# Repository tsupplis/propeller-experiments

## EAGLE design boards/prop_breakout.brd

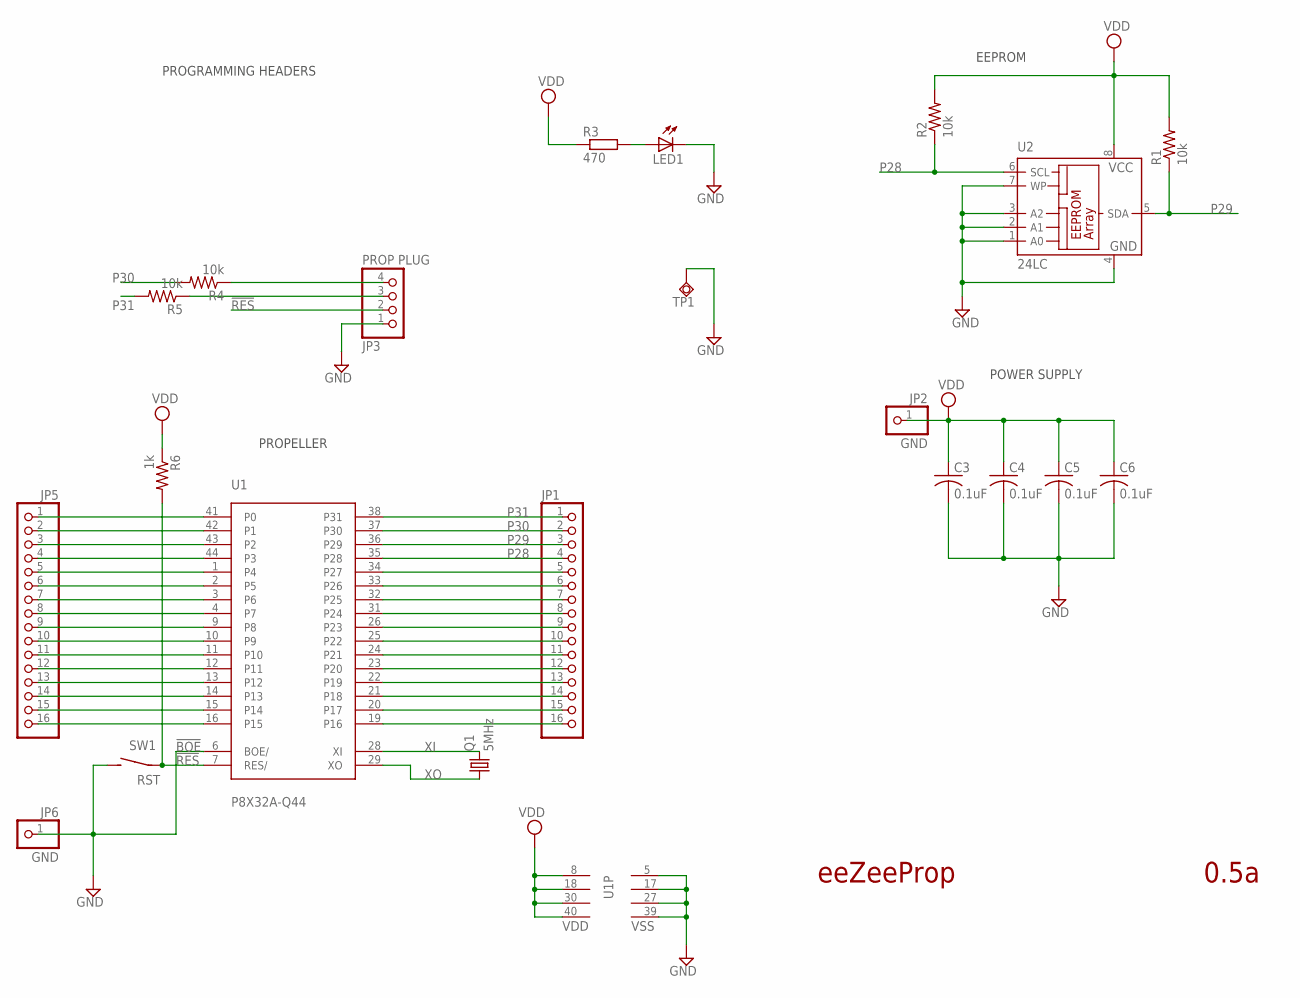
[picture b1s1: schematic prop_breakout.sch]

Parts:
C3, C4, C5, C6: 0.1uF; C0805; PARTNO 0603YC104KAT2A
JP1, JP5: PINHD-1X16_2.54-S; 1X16-S
JP2, JP6: GND; 1X01
JP3: PROP PLUG; 1X04-S
LED1: 0; CHIPLED_1206
Q1: 5MHz; HC49U-V; PARTNO HC49US-5.000MABJ-UB
R1, R2: 10k; R0805; PARTNO ERJ-3GEYJ103V
R3: 470; R0805
R4, R5: 10k; R0805; PARTNO RC0603JR-071KL
R6: 1k; R0805; PARTNO RC0603JR-071KL
SW1: RST; 6MMTACTILE_RECT; PARTNO MJTP1243
TP1: TPSQTP20R; TP20R
U1: P8X32A-Q44; PARTNO P8X32A-Q44
U2: 24LC; SO-08; MPN CAT24C256WI-GT3

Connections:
!RES: JP3.2, R6.2, SW1.P$1, U1.7 (RES/)
GND: C3.2, C4.2, C5.2, C6.2, JP3.1, JP6.1, LED1.C, SW1.P$2 (S), TP1.TP, U1.5 (VSS), U1.6 (BOE/), U1.17 (VSS), U1.27 (VSS), U1.39 (VSS), U2.1 (A0), U2.2 (A1), U2.3 (A2), U2.4 (GND), U2.7 (WP)
unnamed: JP5.1, U1.41 (P0)
unnamed: JP5.2, U1.42 (P1)
unnamed: JP5.3, U1.43 (P2)
unnamed: JP5.4, U1.44 (P3)
unnamed: LED1.A, R3.2
unnamed: JP5.5, U1.1 (P4)
unnamed: JP5.6, U1.2 (P5)
unnamed: JP5.7, U1.3 (P6)
unnamed: JP5.8, U1.4 (P7)
unnamed: JP5.9, U1.9 (P8)
unnamed: JP5.10, U1.10 (P9)
unnamed: JP5.11, U1.11 (P10)
unnamed: JP5.12, U1.12 (P11)
unnamed: JP5.13, U1.13 (P12)
unnamed: JP5.14, U1.14 (P13)
unnamed: JP5.15, U1.15 (P14)
unnamed: JP5.16, U1.16 (P15)
unnamed: JP1.5, U1.34 (P27)
unnamed: JP1.6, U1.33 (P26)
unnamed: JP1.7, U1.32 (P25)
unnamed: JP1.8, U1.31 (P24)
unnamed: JP1.9, U1.26 (P23)
unnamed: JP1.10, U1.25 (P22)
unnamed: JP1.11, U1.24 (P21)
unnamed: JP1.12, U1.23 (P20)
unnamed: JP1.13, U1.22 (P19)
unnamed: JP1.14, U1.21 (P18)
unnamed: JP1.15, U1.20 (P17)
unnamed: JP1.16, U1.19 (P16)
P28: JP1.4, R2.1, U1.35 (P28), U2.6 (SCL)
P29: JP1.3, R1.1, U1.36 (P29), U2.5 (SDA)
P30: JP1.2, R4.2, U1.37 (P30)
P31: JP1.1, R5.2, U1.38 (P31)
RXI: JP3.4, R4.1
TXO: JP3.3, R5.1
VDD: C3.1, C4.1, C5.1, C6.1, JP2.1, R1.2, R2.2, R3.1, R6.1, U1.8 (VDD), U1.18 (VDD), U1.30 (VDD), U1.40 (VDD), U2.8 (VCC)
XI: Q1.2, U1.28 (XI)
XO: Q1.1, U1.29 (XO)

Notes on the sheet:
!BOE
eeZeeProp
0.5a
POWER SUPPLY
PROGRAMMING HEADERS
EEPROM
PROPELLER

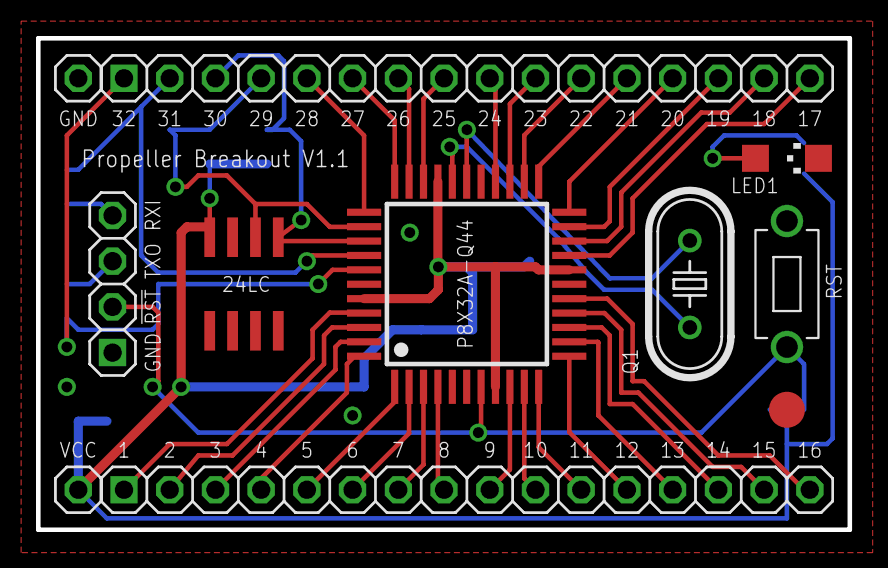
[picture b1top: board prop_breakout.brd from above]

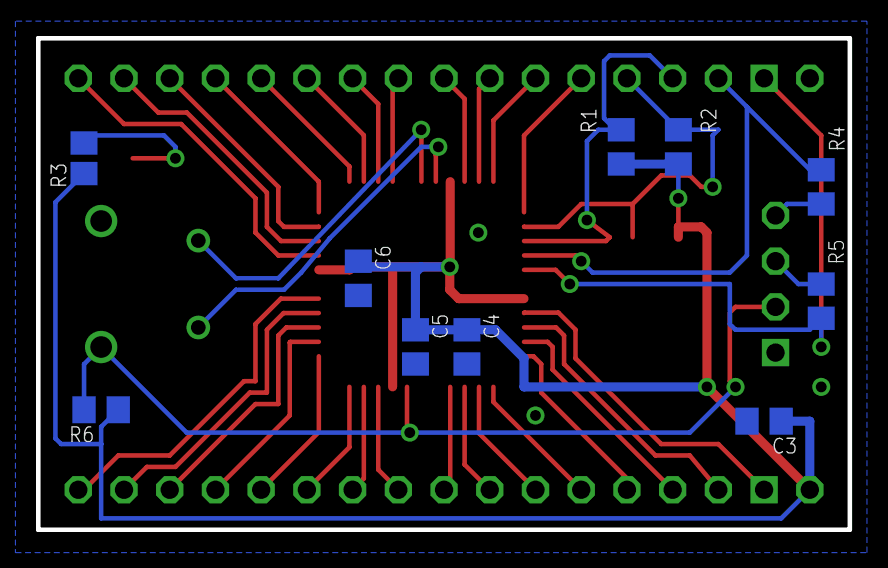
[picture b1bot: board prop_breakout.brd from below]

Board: 2 copper layers, 45.1 x 27.3 mm, 21 parts (10 on the bottom side), 40 nets.

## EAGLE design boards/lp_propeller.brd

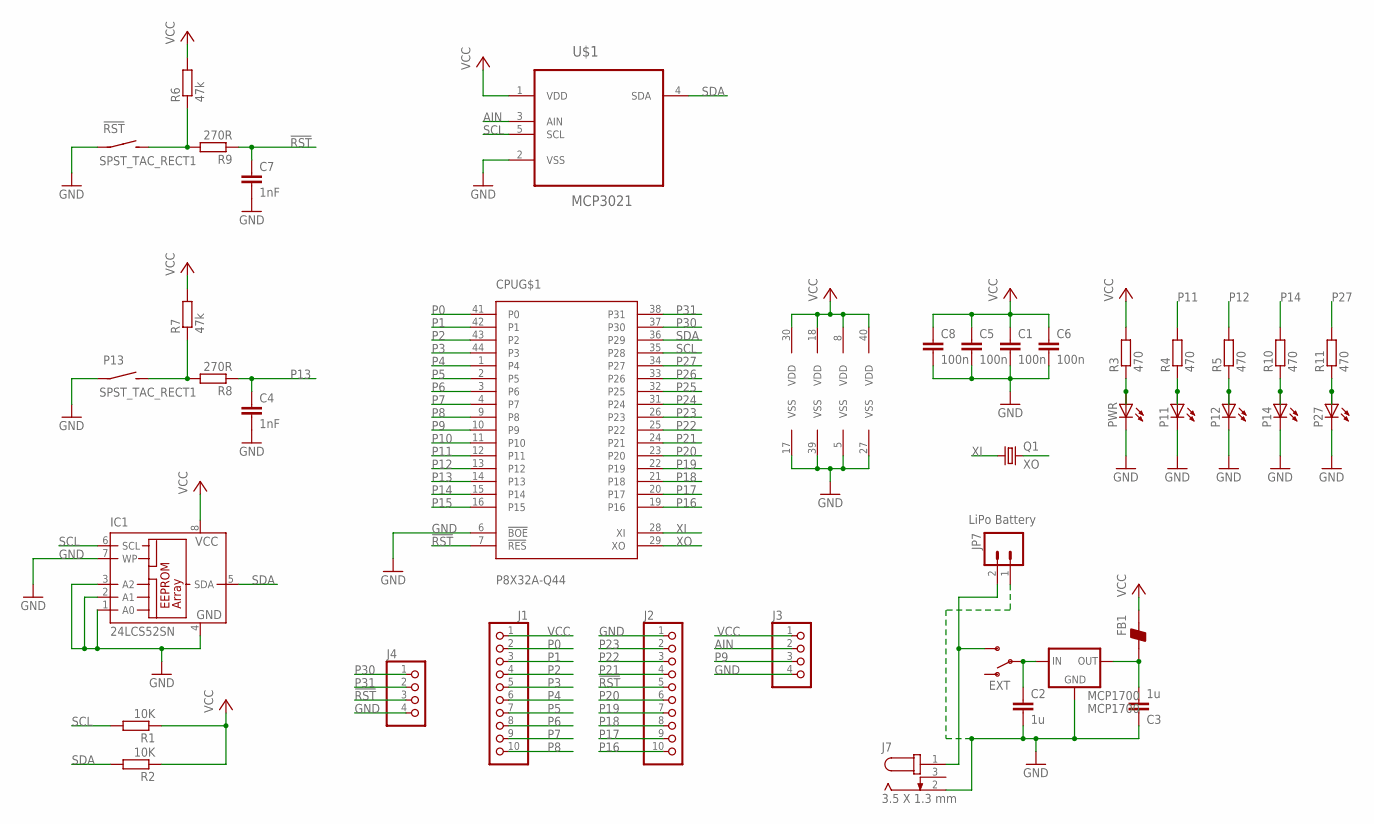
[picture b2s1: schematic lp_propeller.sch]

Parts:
!RST: SPST_TAC_RECT1; 6MMTACTILE_RECT
C1, C5, C6, C8: 100n; C0805
C2, C3: 1u; C0805
C4, C7: 1nF; C0805
CPU: P8X32A-Q44; LQFP-44
FB1: BEAD-0805; 0805
IC1: 24LCS52SN; SO-08
J1, J2: PH1X10OCT076; PH1X10OCT76
J3, J4: PINHD-1X4; 1X04
J7: 3.5 X 1.3 mm; 3.5X1.3MM_DC_JACK
JP7: LiPo Battery; JST-2-PTH
MCP1700: MCP1700; SOT-23
ON: EXT; SWITCH-SPDT
P11, P12, P14, P27: LEDCHIPLED_1206; CHIPLED_1206
P13: SPST_TAC_RECT1; 6MMTACTILE_RECT
PWR: LEDCHIPLED_1206; CHIPLED_1206
Q1: CRYSTALHC49S; HC49/S
R1, R2: 10K; R0805
R3, R4, R5, R10, R11: 470; R0805
R6, R7: 47k; R0805
R8, R9: 270R; R0805
U$1: MCP3021; SOT95P270X145-5N

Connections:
!RST: C7.1, CPU.7 (!RES), J2.5, J4.3, R9.1
AIN: J3.2, U$1.3 (AIN)
GND: !RST.P$1, C1.2, C2.2, C3.1, C4.2, C5.2, C6.2, C7.2, C8.2, CPU.5 (VSS), CPU.6 (!BOE), CPU.17 (VSS), CPU.27 (VSS), CPU.39 (VSS), IC1.1 (A0), IC1.2 (A1), IC1.3 (A2), IC1.4 (GND), IC1.7 (WP), J2.1, J3.4, J4.4, J7.2, JP7.1, MCP1700.1 (GND), P11.C, P12.C, P13.P$1, P14.C, P27.C, PWR.C, U$1.2 (VSS)
unnamed: P14.A, R10.1
unnamed: P27.A, R11.1
unnamed: C2.1, MCP1700.3 (IN), ON.2
unnamed: PWR.A, R3.1
unnamed: P13.P$2 (S), R7.1, R8.2
unnamed: C3.2, FB1.1, MCP1700.2 (OUT)
unnamed: P11.A, R4.1
unnamed: P12.A, R5.1
unnamed: !RST.P$2 (S), R6.1, R9.2
P0: CPU.41 (P0), J1.2
P1: CPU.42 (P1), J1.3
P2: CPU.43 (P2), J1.4
P3: CPU.44 (P3), J1.5
P4: CPU.1 (P4), J1.6
P5: CPU.2 (P5), J1.7
P6: CPU.3 (P6), J1.8
P7: CPU.4 (P7), J1.9
P8: CPU.9 (P8), J1.10
P9: CPU.10 (P9), J3.3
P10: CPU.11 (P10)
P11: CPU.12 (P11), R4.2
P12: CPU.13 (P12), R5.2
P13: C4.1, CPU.14 (P13), R8.1
P14: CPU.15 (P14), R10.2
P15: CPU.16 (P15)
P16: CPU.19 (P16), J2.10
P17: CPU.20 (P17), J2.9
P18: CPU.21 (P18), J2.8
P19: CPU.22 (P19), J2.7
P20: CPU.23 (P20), J2.6
P21: CPU.24 (P21), J2.4
P22: CPU.25 (P22), J2.3
P23: CPU.26 (P23), J2.2
P24: CPU.31 (P24)
P25: CPU.32 (P25)
P26: CPU.33 (P26)
P27: CPU.34 (P27), R11.2
P30: CPU.37 (P30), J4.1
P31: CPU.38 (P31), J4.2
SCL: CPU.35 (P28), IC1.6 (SCL), R1.2, U$1.5 (SCL)
SDA: CPU.36 (P29), IC1.5 (SDA), R2.2, U$1.4 (SDA)
VCC: C1.1, C5.1, C6.1, C8.1, CPU.8 (VDD), CPU.18 (VDD), CPU.30 (VDD), CPU.40 (VDD), FB1.2, IC1.8 (VCC), J1.1, J3.1, R1.1, R2.1, R3.2, R6.2, R7.2, U$1.1 (VDD)
VCCEXT: J7.1, JP7.2, ON.3 (S)
XI: CPU.28 (XI), Q1.1
XO: CPU.29 (XO), Q1.2

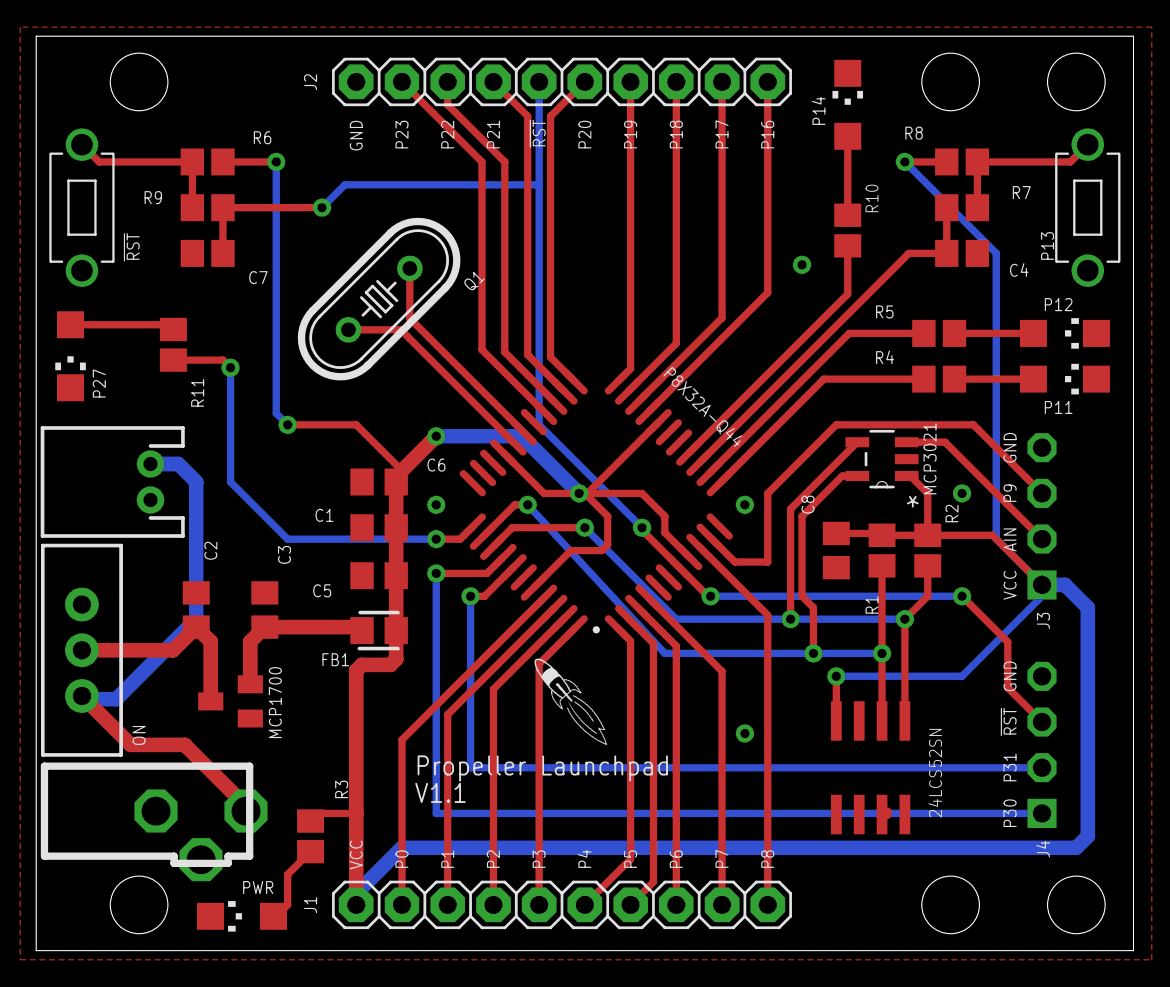
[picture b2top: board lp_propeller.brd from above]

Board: 2 copper layers, 61.0 x 50.8 mm, 40 parts (0 on the bottom side), 43 nets.

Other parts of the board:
U$2: LOGO-ROCKET

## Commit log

2016-04-05 Initial Content

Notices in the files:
parts and their libraries:
SparkFun: Licensing: CC v3.0 Share-Alike You are welcome to use this library for commercial purposes.
